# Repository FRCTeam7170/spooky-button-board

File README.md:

# spooky-button-board
Java code for controlling custom IO expander Raspberry Pi HAT for a button
board.

The IO expanders used are MCP23S17's, which have 16 GPIOs with an SPI
interface. The library used to interface with the chips can be found
[here](https://github.com/Ro5bert/MCP23S17) (JAR releases of it are included
in `lib`.)

The KiCAD schematic and PCB layout can be found in the [kicad folder](kicad).

## Building
To build, clone this repository and run

    ./gradlew shadowJar
    
(Note that, since this was copied from Windows, `gradlew` might not be
executable by default. To make it executable, run `chmod 750 gradlew`.)

This will produce an executable JAR in `build/libs`.

## Running
To execute the JAR produced under Building, simply run

    java -jar /path/to/jar
    
which might need root privileges to access the SPI hardware (prepend with
`sudo`).

## Configuration

### Enabling SPI Interface
The Raspberry Pi's SPI interface must be enabled in order to communicate with
the SPI IO expanders; by default, it is disabled. To enable it run

    raspi-config
    
(needs root privileges; prepend with `sudo` if not root user) and navigate
with the up/down arrow keys to "5 Interfacing Options", then "P4 SPI", and
enable it. Then, use the left/right arrow keys to select "Finish".

### Executing JAR on Boot
It is probably desirable to have to JAR execute when the Raspberry Pi boots.
To do so, we can execute the JAR in `/etc/rc.local`, which is executed on
startup. Edit `rc.local` (`sudo nano /etc/rc.local`) and insert the following
line before the `exit` statement:

    java -jar /path/to/jar > /var/log/sbb.log 2>&1 &
    
(Note `sudo` is not necessary here as `rc.local` is executed as the root
user.)

The "`&`" at the end of the line makes the command run in the background and
is recommended as, without it, the rest of the initialization process will be
blocked as it waits for Java to terminate. (You also will not be able to
manually terminate it via Ctrl-C because it is not started from a shell you
are logged into!) The "`> /var/log/sbb.log`" and "`2>&1`" parts are optional;
they redirect standard output to `/var/log/sbb.log` ("sbb" for
"spooky-button-board") and standard error to standard output (and,
consequently, `/var/log/sbb.log`).

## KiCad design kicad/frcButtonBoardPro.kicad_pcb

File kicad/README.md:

# KiCAD Files for spooky-button-board
The KiCAD schematic and PCB files and other related files can be found here.

The PCB layout was designed with the intention to have it manufactured by
[JLCPCB](https://jlcpcb.com/) and therefore uses constraints (trace width, via
diameter, etc.) within
[their capabilities](https://jlcpcb.com/capabilities/Capabilities).

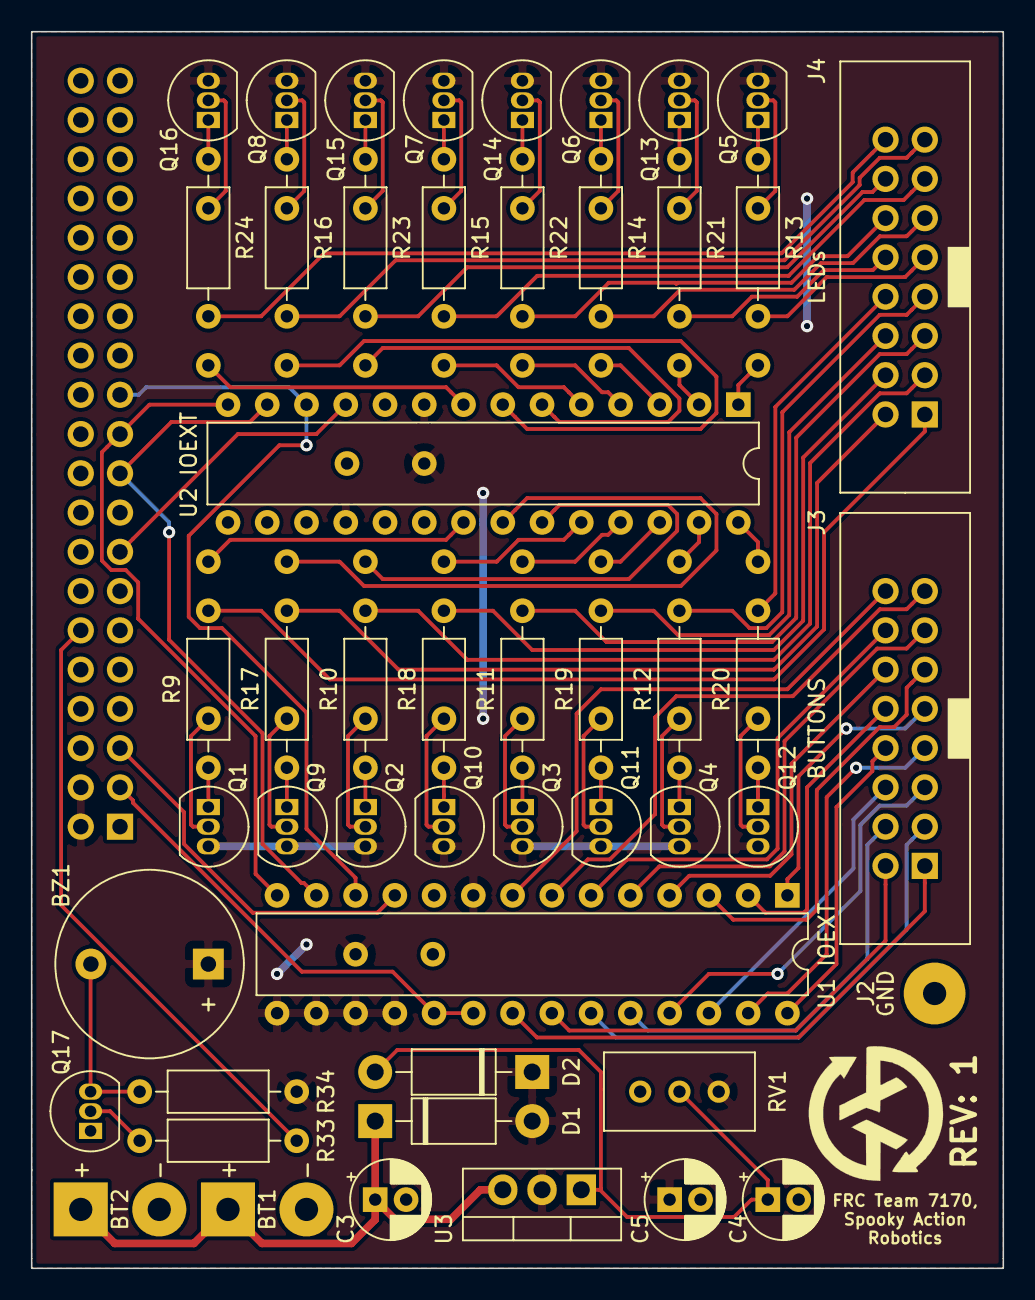
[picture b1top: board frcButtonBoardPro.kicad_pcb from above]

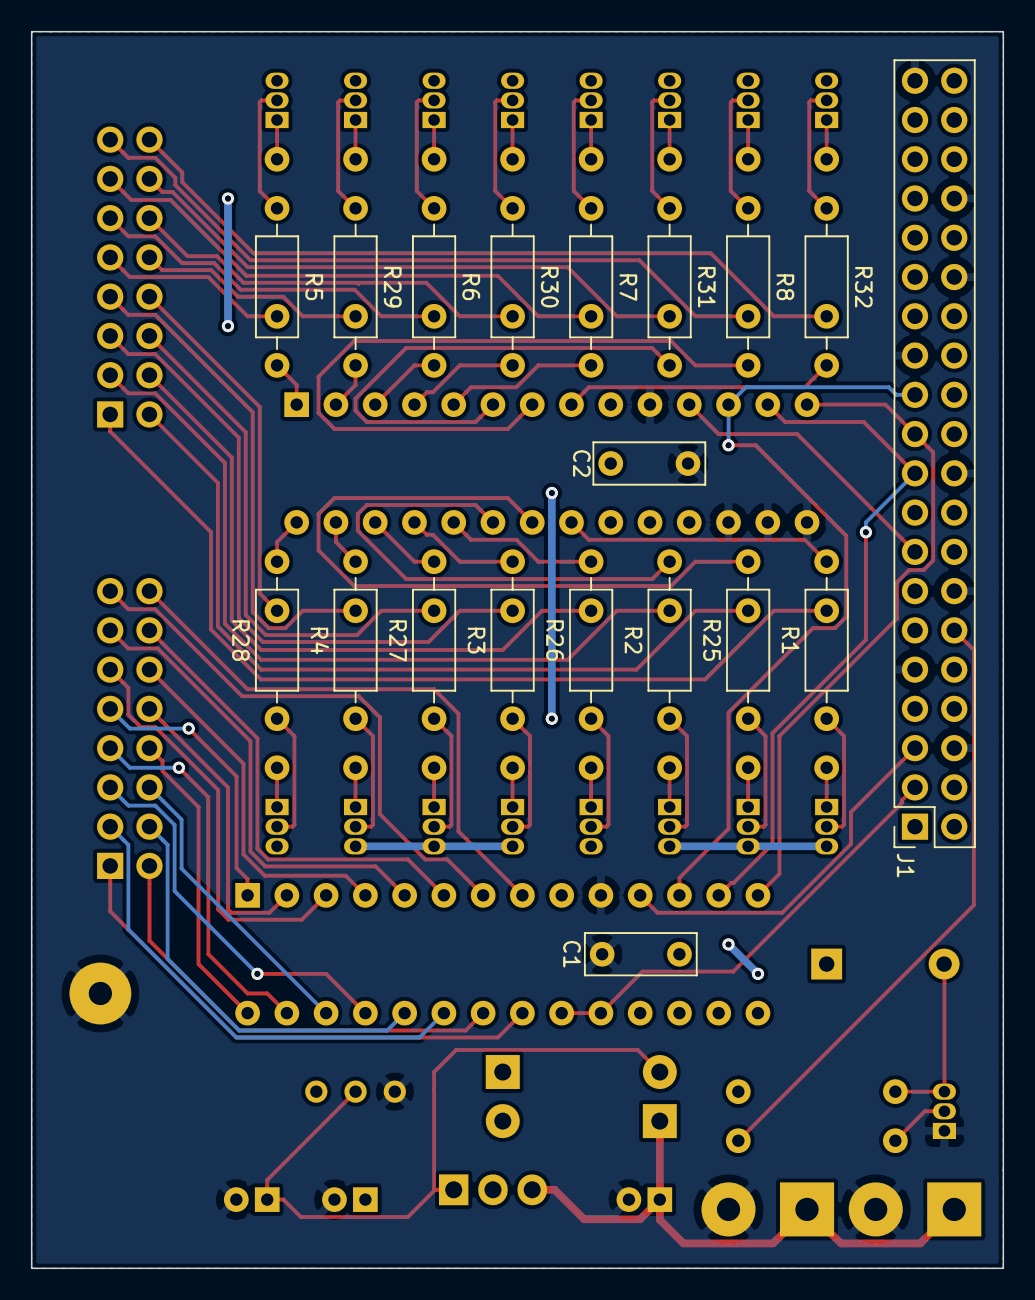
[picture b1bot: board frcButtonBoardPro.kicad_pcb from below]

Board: 2 copper layers, 62.9 x 80.0 mm, 69 parts (19 on the bottom side), 93 nets.

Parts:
BT1, BT2: Battery; SolderWirePad_1x02_P5.08mm_Drill1.5mm
BZ1: Buzzer; Buzzer_12x9.5RM7.6
C1, C2: 100n; C_Rect_L7.0mm_W2.5mm_P5.00mm
C3, C4, C5: 10u; CP_Radial_D5.0mm_P2.00mm
D1, D2: 1N4002; D_DO-41_SOD81_P10.16mm_Horizontal
J1: Raspberry_Pi_2_3; PinSocket_2x20_P2.54mm_Vertical
J2: Conn_01x01; SolderWirePad_1x01_Drill1.5mm
J3, J4: Conn_02x08_Odd_Even; 16PIN_RIBBON_CONN
Q1, Q2, Q3, Q4, Q5, Q6, Q7, Q8, Q9, Q10, Q11, Q12, Q13, Q14, Q15, Q16, Q17: 2N3904; TO-92_Inline
R1, R2, R3, R4, R5, R6, R7, R8, R25, R26, R27, R28, R29, R30, R31, R32: 10K; R_Axial_DIN0207_L6.3mm_D2.5mm_P10.16mm_Horizontal
R9, R10, R11, R12, R13, R14, R15, R16, R17, R18, R19, R20, R21, R22, R23, R24: 100R; R_Axial_DIN0207_L6.3mm_D2.5mm_P10.16mm_Horizontal
R33, R34: 1K; R_Axial_DIN0207_L6.3mm_D2.5mm_P10.16mm_Horizontal
RV1: R_POT_TRIM_US; Potentiometer_Bourns_3296W_Vertical
U1, U2: MCP23S17_SP; DIP-28_W7.62mm
U3: LM317_3PinPackage; TO-220-3_Vertical

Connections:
+5V: BZ1.1, C1.1, C2.1, C5.1, D1.2, D2.1, J1.2, J1.4, Q1.3, Q2.3, Q3.3, Q4.3, Q5.3, Q6.3, Q7.3, Q8.3, Q9.3, Q10.3, Q11.3, Q12.3, Q13.3, Q14.3, Q15.3, Q16.3, R34.1, RV1.3, U1.9, U1.15, U1.16, U1.17, U1.18, U2.9, U2.18, U3.2
/INT: J1.3, U1.19, U1.20
/MISO: J1.21, U1.14, U2.14
/MOSI: J1.19, U1.13, U2.13
/SCLK: J1.23, U1.12, U2.12
/buttons/BUTTON1: J3.1, U1.21
/buttons/BUTTON2: J3.2, U1.22
/buttons/BUTTON3: J3.3, U1.23
/buttons/BUTTON4: J3.4, U1.24
/buttons/BUTTON5: J3.5, U1.25
/buttons/BUTTON6: J3.6, U1.26
/buttons/BUTTON7: J3.7, U1.27
/buttons/BUTTON8: J3.8, U1.28
/buttons/BUTTON9: J3.9, U1.1
/buttons/BUTTON10: J3.10, U1.2
/buttons/BUTTON11: J3.11, U1.3
/buttons/BUTTON12: J3.12, U1.4
/buttons/BUTTON13: J3.13, U1.5
/buttons/BUTTON14: J3.14, U1.6
/buttons/BUTTON15: J3.15, U1.7
/buttons/BUTTON16: J3.16, U1.8
/buzzer/BUZZER_PWM: J1.12, R33.2
/leds/LED1: R1.2, U2.21
/leds/LED2: R25.2, U2.22
/leds/LED3: R2.2, U2.23
/leds/LED4: R26.2, U2.24
/leds/LED5: R3.2, U2.25
/leds/LED6: R27.2, U2.26
/leds/LED7: R4.2, U2.27
/leds/LED8: R28.2, U2.28
/leds/LED9: R5.2, U2.1
/leds/LED10: R29.2, U2.2
/leds/LED11: R6.2, U2.3
/leds/LED12: R30.2, U2.4
/leds/LED13: R7.2, U2.5
/leds/LED14: R31.2, U2.6
/leds/LED15: R8.2, U2.7
/leds/LED16: R32.2, U2.8
/~CS_Buttons: J1.5, U1.11
/~CS_LEDs: J1.15, U2.11
GND: BT1.2, BT2.2, C1.2, C2.2, C3.2, C4.2, C5.2, J1.6, J1.9, J1.14, J1.20, J1.25, J1.30, J1.34, J1.39, J2.1, Q17.1, RV1.1, U1.10, U2.10, U2.15, U2.16, U2.17
unnamed: BT1.1, BT2.1, C3.1, D1.1, U3.3
unnamed: BZ1.2, Q17.3, R34.2
unnamed: C4.1, D2.2, RV1.2, U3.1
unnamed: J4.1, R9.2
unnamed: J4.2, R17.2
unnamed: J4.3, R10.2
unnamed: J4.4, R18.2
unnamed: J4.5, R11.2
unnamed: J4.6, R19.2
unnamed: J4.7, R12.2
unnamed: J4.8, R20.2
unnamed: J4.9, R13.2
unnamed: J4.10, R21.2
unnamed: J4.11, R14.2
unnamed: J4.12, R22.2
unnamed: J4.13, R15.2
unnamed: J4.14, R23.2
unnamed: J4.15, R16.2
unnamed: J4.16, R24.2
unnamed: Q1.1, R9.1
unnamed: Q1.2, R1.1
unnamed: Q2.1, R10.1
unnamed: Q2.2, R2.1
unnamed: Q3.1, R11.1
unnamed: Q3.2, R3.1
unnamed: Q4.1, R12.1
unnamed: Q4.2, R4.1
unnamed: Q5.1, R13.1
unnamed: Q5.2, R5.1
unnamed: Q6.1, R14.1
unnamed: Q6.2, R6.1
unnamed: Q7.1, R15.1
unnamed: Q7.2, R7.1
unnamed: Q8.1, R16.1
unnamed: Q8.2, R8.1
unnamed: Q9.1, R17.1
unnamed: Q9.2, R25.1
unnamed: Q10.1, R18.1
unnamed: Q10.2, R26.1
unnamed: Q11.1, R19.1
unnamed: Q11.2, R27.1
unnamed: Q12.1, R20.1
unnamed: Q12.2, R28.1
unnamed: Q13.1, R21.1
unnamed: Q13.2, R29.1
unnamed: Q14.1, R22.1
unnamed: Q14.2, R30.1
unnamed: Q15.1, R23.1
unnamed: Q15.2, R31.1
unnamed: Q16.1, R24.1
unnamed: Q16.2, R32.1
unnamed: Q17.2, R33.1

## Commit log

2019-05-28 First commit.
2019-05-28 Add stuff to handle LEDs switching on button presses.
2019-05-29 Significant restructure.
2019-06-25 Add in pin numbers corresponding to physical connections. Remove (comment out) temporary code for testing.
2019-06-26 Add NTCore libs. Add wpiutil dependency to build.gradle.
2019-06-26 Add native NTCore lib to build.gradle for linux/raspbian target. Un-ignore mcp23s17 libs and gradle wrapper.
2019-06-26 Change version number. Populate README with some basic setup instructions.
2019-06-26 Minor README formatting. Remove TODOs from ButtonBoard.
2019-06-26 Add KiCad files with corresponding README.
2019-06-26 Change README header sizes.
2019-06-26 Change sourceCompatibility to 1.11 in build.gradle. Clarify command in README.
2019-06-26 Make whole display pulse three times when NT successfully connects.
2019-07-11 Add misc.xml.
2019-07-11 Disable (comment out) networking code. Enable (un-comment) test code.
2019-07-11 Change sourceCompatibility back to 1.8 (R. Pis come with java 8, not java 11).
2019-07-11 Prepare source to test button input.
2019-07-11 Prepare source to test networking.
2019-08-28 Comment out NT stuff
2019-08-28 Change buttons IO exp config
2019-08-28 Undo buttons IO exp config change
2019-10-02 Update README: add reference to kicad folder
2019-10-02 Update kicad/README: capitalize CAD in KiCAD
